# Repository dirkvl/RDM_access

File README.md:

#RDM Makerspace access system

##SW

###Set up Raspbian

Burn [latest Rasbian image](https://www.raspberrypi.org/downloads/) on uSD card

Expand rootsystem

Advanced options > Enable I2C

```
$ sudo apt-get update
$ sudo apt-get upgrade
$ sudo apt-get dist-upgrade
$ sudo reboot
```

####WiringPi
```
sudo apt-get install git-core
git clone git://git.drogon.net/wiringPi
cd wiringPi
git pull origin
./build

gpio -v
gpio readall
```

####I2C

```
sudo apt-get install i2c-tools
sudo apt-get install python-smbus
sudo adduser pi i2c
sudo reboot
```

Add to /etc/modules
```
i2c-bcm2708
i2c-dev
```

Add to /etc/rc.local
```
modprobe i2c-dev
```

###Enable RTC

Install battery

Check if RTC shows up at 0x6f using
```
i2cdetect -y 1
```

Add to /etc/rc.local
```
modprobe i2c:mcp7941x
echo mcp7941x 0x6f > /sys/class/i2c-dev/i2c-1/device/new-device
```

Reboot

```
sudo date -s "7 MAY 2015 21:27:00"

####Freeing UART

$ sudo raspi-config

From the main menu, select option 7 (Serial), then select 'No' to disable shell and kernel messages via UART.

$ sudo reboot

###Build libnfc

See https://learn.adafruit.com/adafruit-nfc-rfid-on-raspberry-pi/building-libnfc

```

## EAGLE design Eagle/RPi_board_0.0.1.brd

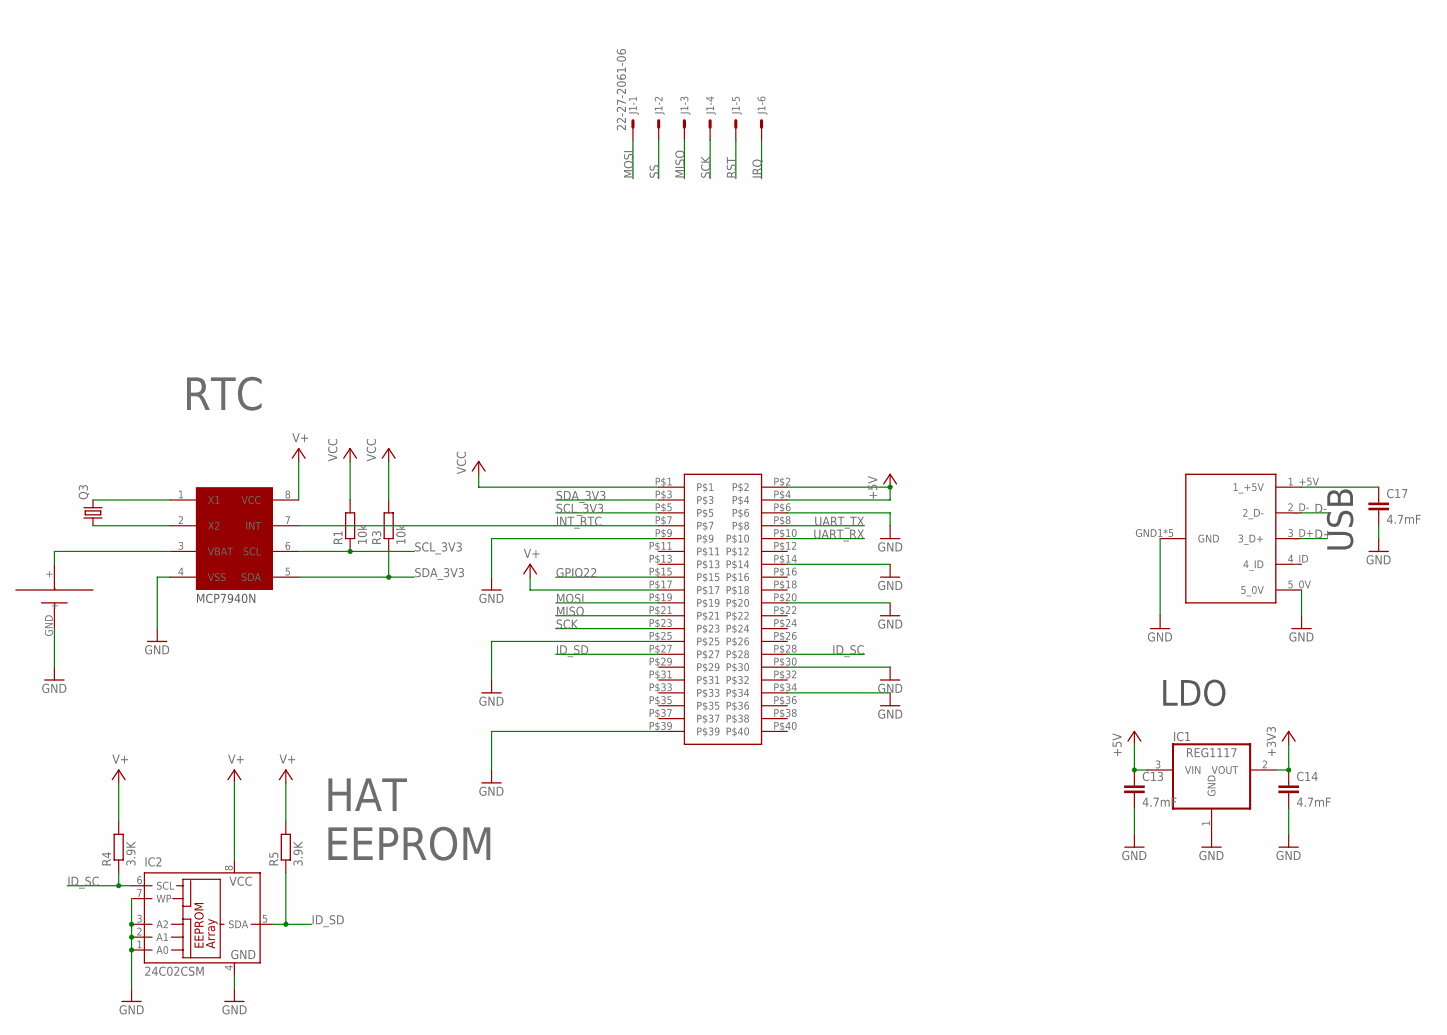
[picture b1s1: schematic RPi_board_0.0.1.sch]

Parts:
C13, C14, C17: 4.7mF; C0603
IC1: REG1117; SOT223
IC2: 24C02CSM; SO-08M
J1: 22-27-2061-06; 6410-06
Q3: CRYSTALMM20SS; MM20SS
R1, R3: 10k; R0603
R4, R5: 3.9K; R0603
U$4: CR1216
U$5: MCP7940N; SO08
U$9: MICRO_USB
U$11: HEADER; 20X2

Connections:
+3V3: C14.1, IC1.2 (VOUT)
+5V: C13.1, IC1.3 (VIN), U$11.P$2, U$11.P$4
D+: U$9.3_D+
D-: U$9.2_D-
GND: C13.2, C14.2, C17.2, IC1.1 (GND), IC2.1 (A0), IC2.2 (A1), IC2.3 (A2), IC2.4 (GND), IC2.7 (WP), U$4.GND (-), U$5.4 (VSS), U$9.5_0V, U$9.GND1 (GND), U$9.GND2 (GND), U$9.GND5 (GND), U$9.P$1 (GND), U$9.P$7 (GND), U$11.P$6, U$11.P$9, U$11.P$14, U$11.P$20, U$11.P$25, U$11.P$30, U$11.P$34, U$11.P$39
GPIO22: U$11.P$15
ID_SC: IC2.6 (SCL), R4.1, U$11.P$28
ID_SD: IC2.5 (SDA), R5.1, U$11.P$27
INT_RTC: U$5.7 (INT), U$11.P$7
IRQ: J1.6
MISO: J1.3, U$11.P$21
MOSI: J1.1, U$11.P$19
unnamed: Q3.1, U$5.2 (X2)
unnamed: Q3.4 (2), U$5.1 (X1)
unnamed: C17.1, U$9.1_+5V
RST: J1.5
SCK: J1.4, U$11.P$23
SCL_3V3: R1.1, U$5.6 (SCL), U$11.P$5
SDA_3V3: R3.1, U$5.5 (SDA), U$11.P$3
SS: J1.2
UART_RX: U$11.P$10
UART_TX: U$11.P$8
V+: IC2.8 (VCC), R4.2, R5.2, U$5.8 (VCC), U$11.P$17
VBAT+: U$4.+, U$5.3 (VBAT)
VCC: R1.2, R3.2, U$11.P$1

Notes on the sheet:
RTC
HAT EEPROM
MCP7940N
USB
LDO

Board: 2 copper layers, 15 parts (13 on the bottom side), 17 nets, no tracks yet.

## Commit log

2015-07-19 :octocat: Added .gitattributes & .gitignore files
2015-07-19 first steps
